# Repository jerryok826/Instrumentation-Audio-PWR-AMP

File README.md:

# Instrumentation-Audio-PWR-AMP

## Project Description
I needed a audio amp I could use to test speakers and haptics. Most audio amps today seem to be class D using some form of PWM output drive. These cannot be easily be tested with a scope. So I started looking for a linear class AB audio amp. The old LM1875 meets these requirements. The other specs I was looking for were running from 12 volts. Also DC direct speaker dirve so the amp's low frequency performance was the very best.  Also I wanted a calibrated gain. With the audio attenuation pot set to 100% the input to out gain is 20. The design uses a on board 12 volt to -12v converter to generated the required negative supply voltage for the LM1875. The DC offset at the speaker terminals is typically about 1 millvolt. I call this board a "Instrumentation Audio PWR AMP" because it has known characteristicss for testing speakers and haptics. ALso the polarity of the output can be changed via a jump. Also there is a small VU meter to monitor the speaker driver level. This is mostly for debugging the a haptics test setup.

The unit should put out about 10 watts into a 4 ohm speaker. The spec sheet for the LM1875 is in the Docs directory. 

### Project Status
The project is basically complete.

## Design Files
This project was designed with Kicad 7.X

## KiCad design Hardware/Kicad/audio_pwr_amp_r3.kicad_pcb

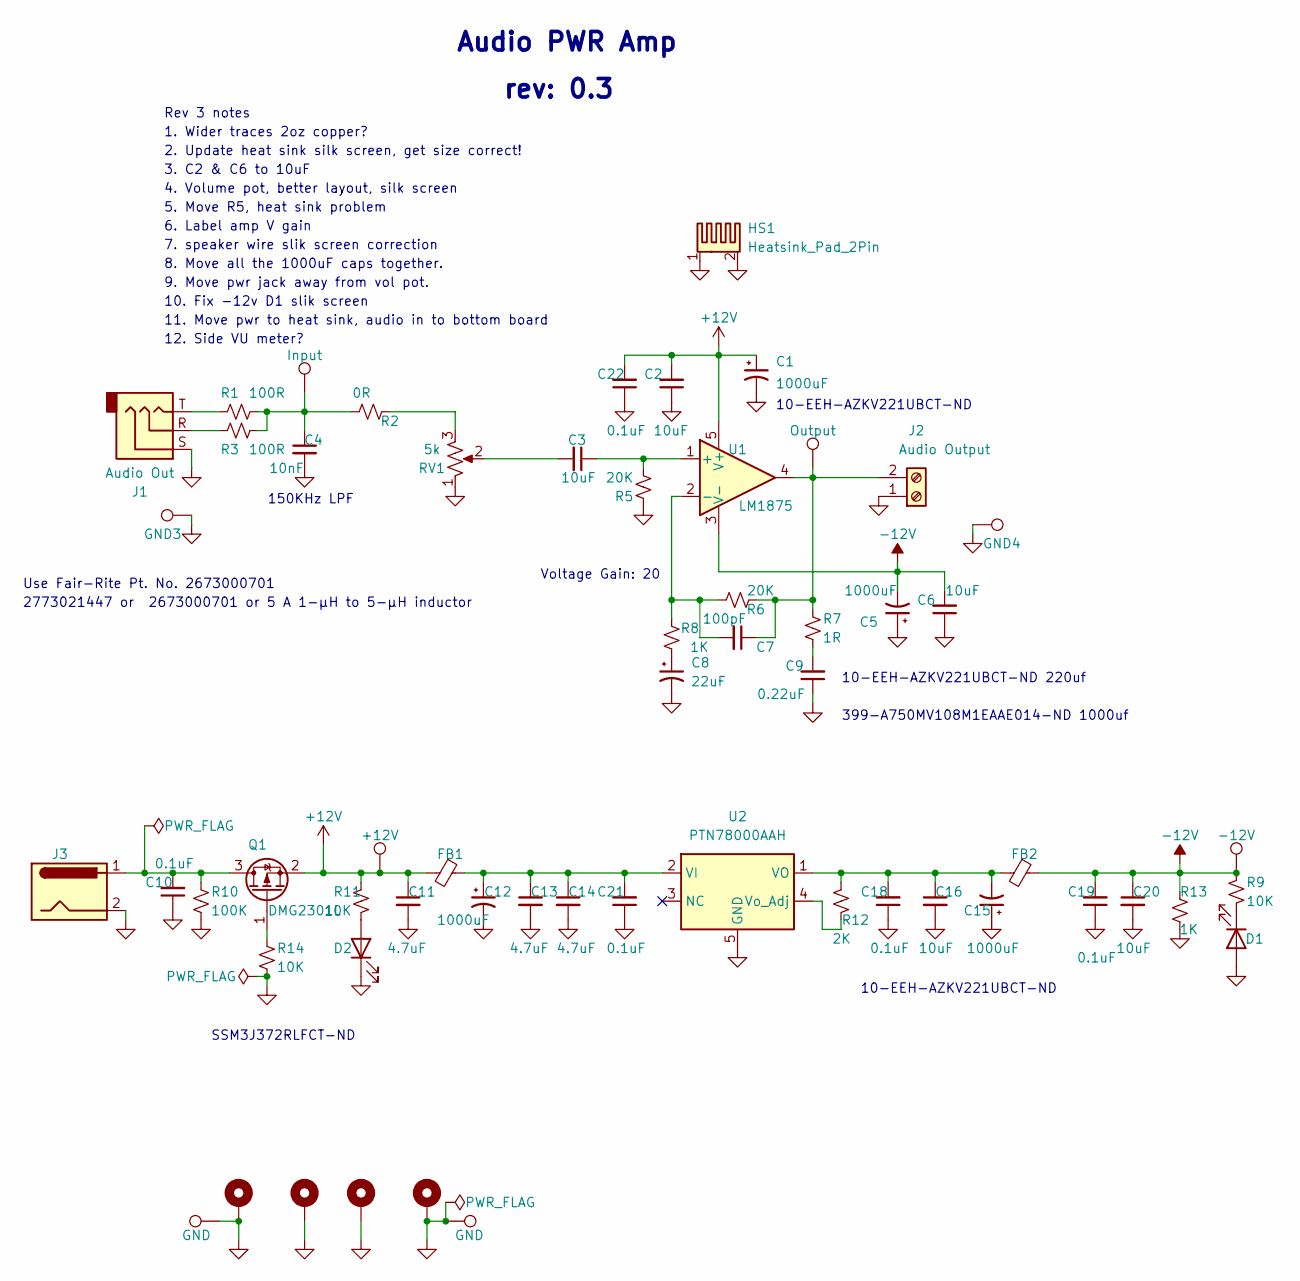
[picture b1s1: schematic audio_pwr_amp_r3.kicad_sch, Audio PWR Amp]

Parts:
+12Vt1: +12V; TestPoint_THTPad_D2.0mm_Drill1.0mm
-12Vt1: -12V; TestPoint_THTPad_D2.0mm_Drill1.0mm
C1, C5, C12, C15: 1000uF; CP_Radial_D10.0mm_P5.00mm
C2, C3, C6, C16, C20: 10uF; C_0805_2012Metric_Pad1.18x1.45mm_HandSolder
C4: 10nF; C_0805_2012Metric_Pad1.18x1.45mm_HandSolder
C7: 100pF; C_0805_2012Metric_Pad1.18x1.45mm_HandSolder
C8: 22uF; C_1206_3216Metric_Pad1.33x1.80mm_HandSolder
C9: 0.22uF; C_0805_2012Metric_Pad1.18x1.45mm_HandSolder
C10, C18, C19, C21, C22: 0.1uF; C_0805_2012Metric_Pad1.18x1.45mm_HandSolder
C11, C13, C14: 4.7uF; C_0805_2012Metric_Pad1.18x1.45mm_HandSolder
D1, D2: OC_Fault; LED_1206_3216Metric_Pad1.42x1.75mm_HandSolder
FB1, FB2: FerriteBead, 6A 1 9mΩ 33Ω@100MHz ±25% 1206 Ferrit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; L_Axial_L14.0mm_D4.5mm_P15.24mm_Horizontal_Fastron_LACC
GND3, GND4: TP_FET_Drive; TestPoint_THTPad_D2.0mm_Drill1.0mm
GND5, GND6: GND; TestPoint_THTPad_D2.0mm_Drill1.0mm
H1, H2, H3, H4: MountingHole_Pad; MountingHole_3.2mm_M3_ISO7380_Pad_TopBottom
HS1: Heatsink_Pad_2Pin; Heatsink_Audio_Amp
Input1: Input; TestPoint_THTPad_D2.0mm_Drill1.0mm
J1: Audio Out; Jack_3.5mm_CUI_SJ-3523-SMT_Horizontal
J2: Audio Output; TerminalBlock_bornier-2_P5.08mm; LCSC No Stock
J3: INPUT_PWR; BarrelJack_GCT_DCJ200-10-A_Horizontal
OUTPUT2: Output; TestPoint_THTPad_D2.0mm_Drill1.0mm
Q1: DMG2301L; SOT-23
R1, R3: 100R; R_0805_2012Metric_Pad1.20x1.40mm_HandSolder
R2: 0R; R_0805_2012Metric_Pad1.20x1.40mm_HandSolder
R5, R6: 20K; R_0805_2012Metric_Pad1.20x1.40mm_HandSolder
R7: 1R; R_0805_2012Metric_Pad1.20x1.40mm_HandSolder
R8, R13: 1K; R_0805_2012Metric_Pad1.20x1.40mm_HandSolder
R9, R11, R14: 10K; R_0805_2012Metric_Pad1.20x1.40mm_HandSolder
R10: 100K; R_0805_2012Metric_Pad1.20x1.40mm_HandSolder
R12: 2K; R_0805_2012Metric_Pad1.20x1.40mm_HandSolder
RV1: 5k; Potentiometer_Bourns_3386P_Vertical
U1: LM1875; TO-220-5_P3.4x3.7mm_StaggerOdd_Lead3.8mm_Vertical
U2: PTN78000AAH; Texas_EUS_R-PDSS-T5_THT

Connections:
+12V: +12Vt1.1, C1.1, C2.2, C11.1, C22.2, FB1.2, Q1.2 (S), R11.2, U1.5 (V+)
-12V: -12Vt1.1, C5.2, C6.2, C19.2, C20.1, FB2.1, R9.2, R13.2, U1.3 (V-)
GND: C1.2, C2.1, C4.2, C5.1, C6.1, C8.2, C9.1, C10.1, C11.2, C12.2, C13.2, C14.2, C15.1, C16.2, C18.1, C19.1, C20.2, C21.1, C22.1, D1.2 (A), D2.1 (K), GND3.1, GND4.1, GND5.1, GND6.1, H1.1, H2.1, H3.1, H4.1, HS1.1, HS1.2, J1.S, J2.1, J3.2, R5.1, R10.2, R13.1, R14.2, RV1.1, U2.5 (GND)
unnamed: C3.2, RV1.2
unnamed: C4.1, Input1.1, R1.1, R2.2, R3.1
unnamed: C8.1, R8.1
unnamed: C9.2, R7.2
unnamed: D1.1 (K), R9.1
unnamed: D2.2 (A), R11.1
unnamed: J1.R, R3.2
unnamed: J1.T, R1.2
unnamed: C7.1, J2.2, OUTPUT2.1, R6.2, R7.1, U1.4
unnamed: C10.2, J3.1, Q1.3 (D), R10.1
unnamed: Q1.1 (G), R14.1
unnamed: R2.1, RV1.3
unnamed: C3.1, R5.2, U1.1 (+)
unnamed: C7.2, R6.1, R8.2, U1.2 (-)
unnamed: C12.1, C13.1, C14.1, C21.2, FB1.1, U2.2 (VI)
unnamed: C15.2, C16.1, C18.2, FB2.2, R12.2, U2.1 (VO)
unnamed: R12.1, U2.4 (Vo_Adj)

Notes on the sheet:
399-A750MV108M1EAAE014-ND 1000uf
5. Move R5, heat sink problem
4. Volume pot, better layout, silk screen
10-EEH-AZKV221UBCT-ND 220uf
rev: 0.3
9. Move pwr jack away from vol pot.
2773021447 or 2673000701 or 5 A 1-μH to 5-μH inductor
8. Move all the 1000uF caps together.
3. C2 & C6 to 10uF
6. Label amp V gain
Audio PWR Amp
7. speaker wire slik screen correction
11. Move pwr to heat sink, audio in to bottom board
Voltage Gain: 20
10-EEH-AZKV221UBCT-ND
150KHz LPF
12. Side VU meter?
SSM3J372RLFCT-ND
2. Update heat sink silk screen, get size correct!
10. Fix -12v D1 slik screen
Rev 3 notes
Use Fair-Rite Pt. No. 2673000701
1. Wider traces 2oz copper?

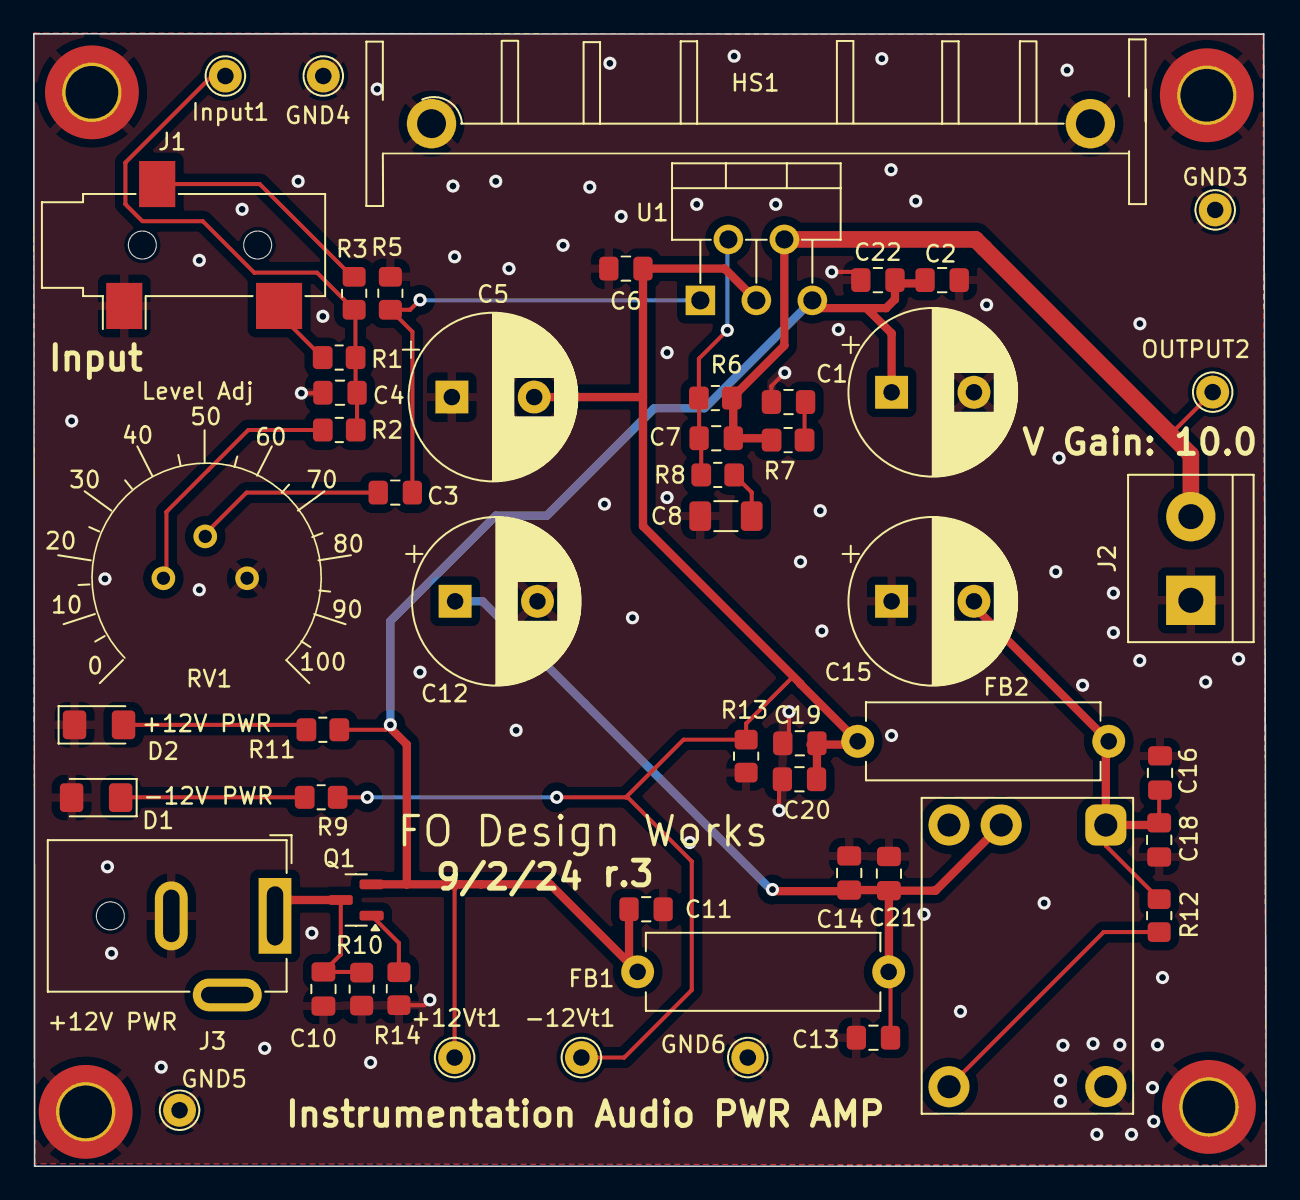
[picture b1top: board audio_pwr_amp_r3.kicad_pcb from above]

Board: 2 copper layers, 74.8 x 68.8 mm, 58 parts (0 on the bottom side), 20 nets.
